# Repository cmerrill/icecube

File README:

This is a music-reactive "light cube" throwie.

Yaaaay! :D

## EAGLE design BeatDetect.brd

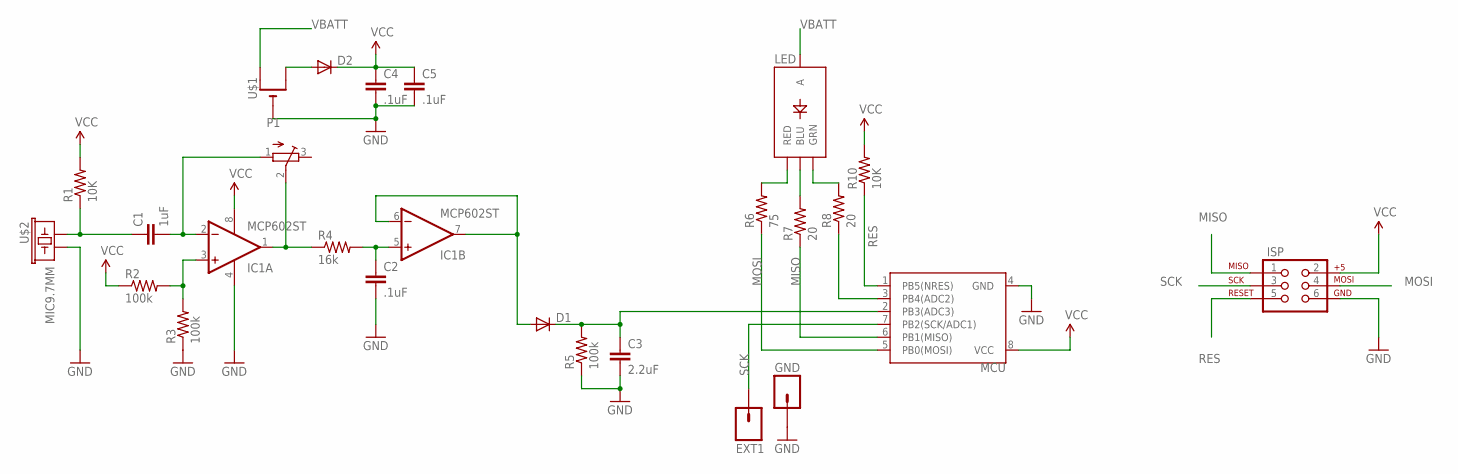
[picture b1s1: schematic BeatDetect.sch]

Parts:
C1: 1uF; 0805
C2, C4, C5: .1uF; 0603-CAP
C3: 2.2uF; 0805
D1, D2: DIODESOD; SOD-323
EXT1: M01PTH; 1X01
GND: M01PTH; 1X01
IC1: MCP602ST; TSSOP8
ISP: AVR_SPI_PRG_6PTH; 2X3
LED: LED-TRICOLORPLCC4; LED-PLCC4
MCU: ATTINY45X; TSSOP8
P1: TRIMPOTTC33X; TC33X
R1, R10: 10K; 0402-RES
R2, R3, R5: 100k; 0402-RES
R4: 16k; 0402-RES
R6: 75; 0805
R7, R8: 20; 0402-RES
U$1: CR2032SMT; CR2032-SMD
U$2: MIC9.7MM; MIC-9.7MM

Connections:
GND: C2.2, C3.2, C4.2, C5.2, GND.1, IC1.4 (V-), ISP.6, MCU.4 (GND), R3.1, R5.1, U$1.-, U$2.2
MISO: ISP.1, MCU.6 (PB1(MISO)), R7.1
MOSI: ISP.4, MCU.5 (PB0(MOSI)), R6.1
unnamed: D1.2 (A), IC1.6 (-IN), IC1.7 (OUT)
unnamed: C2.1, IC1.5 (+IN), R4.2
unnamed: IC1.1 (OUT), P1.2 (S), R4.1
unnamed: C1.1, R1.1, U$2.1
unnamed: C1.2, IC1.2 (-IN), P1.1 (A)
unnamed: IC1.3 (+IN), R2.2, R3.2
unnamed: D2.2 (A), U$1.+$2 (+1)
unnamed: MCU.3 (PB4(ADC2)), R8.1
unnamed: LED.R (RED), R6.2
unnamed: LED.G (GRN), R8.2
unnamed: LED.B (BLU), R7.2
unnamed: C3.1, D1.1 (C), MCU.2 (PB3(ADC3)), R5.2
RES: ISP.5, MCU.1 (PB5(NRES)), R10.1
SCK: EXT1.1, ISP.3, MCU.7 (PB2(SCK/ADC1))
VBATT: LED.A, U$1.+$1 (+)
VCC: C4.1, C5.1, D2.1 (C), IC1.8 (V+), ISP.2, MCU.8 (VCC), R1.2, R2.1, R10.2

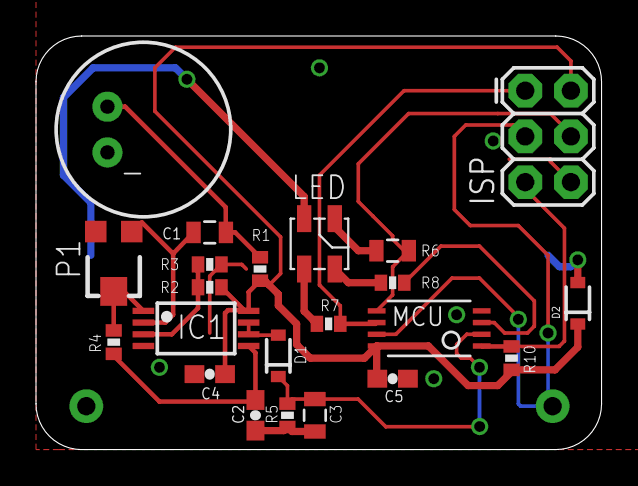
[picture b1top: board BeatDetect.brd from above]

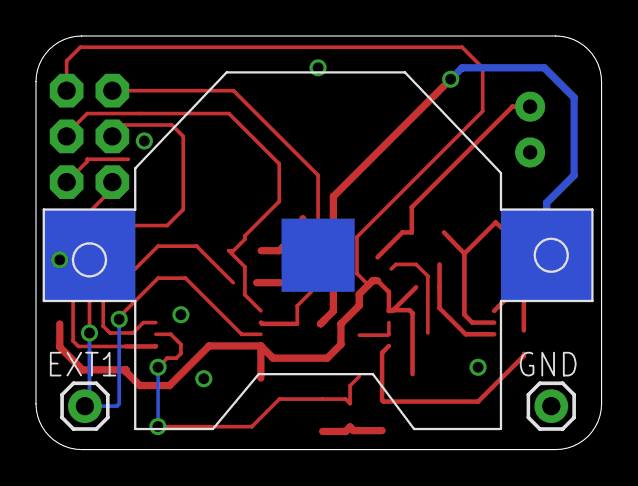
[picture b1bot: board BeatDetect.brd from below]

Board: 2 copper layers, 31.4 x 23.0 mm, 25 parts (3 on the bottom side), 19 nets.

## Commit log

2013-06-01 Initial commit.
    Need to fix power separation between programming and LED power.
2013-06-01 Fixing a bunch of small naming errors & part size mismatches.
2013-06-02 Added power diode to isolate LED supply from MCU & etc. supply.
    Makes it a lot easier to safely program the MCU w/o turning the LED on
    and prevents backfriving current into the battery.
2013-09-09 Initial pass at firmware for the ice cube.
2013-09-09 Let's not store build files...
2013-09-09 Let's update our gitignore to ignore eagle extra files, too!
2013-09-09 Let the main loop control the actual sleep command.
    This lets us turn the LEDs off and etc w/o breaking
    any abstractions.
2013-09-09 Oops, forgot to actually store the new sleep delay.
2013-09-09 Yay! Finished everything but the actual beat detection.
2013-09-09 Fixing a few bugs noticed in the simulator.
    E.g. ADC was being turned off after starting conversion,
    off by one error on cycle timing.
2013-09-16 Fix bug in watchdog configuration.
2013-09-16 Implemented first pass at peak detection funciton.

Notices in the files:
parts and their libraries:
SparkFun-Sensors: Licensing: CC v3.0 Share-Alike You are welcome to use this library for commercial purposes.
